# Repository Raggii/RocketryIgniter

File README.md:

# RocketryIgniter
To design and prototype a dual ignition system that can receive commands over UART and CANBUS. The device must be able to receive commands that arm and fire two separate but identical ignition circuits while also outputting its own system status. The design must attempt to be as compact as possible while also allowing for easy debugging.

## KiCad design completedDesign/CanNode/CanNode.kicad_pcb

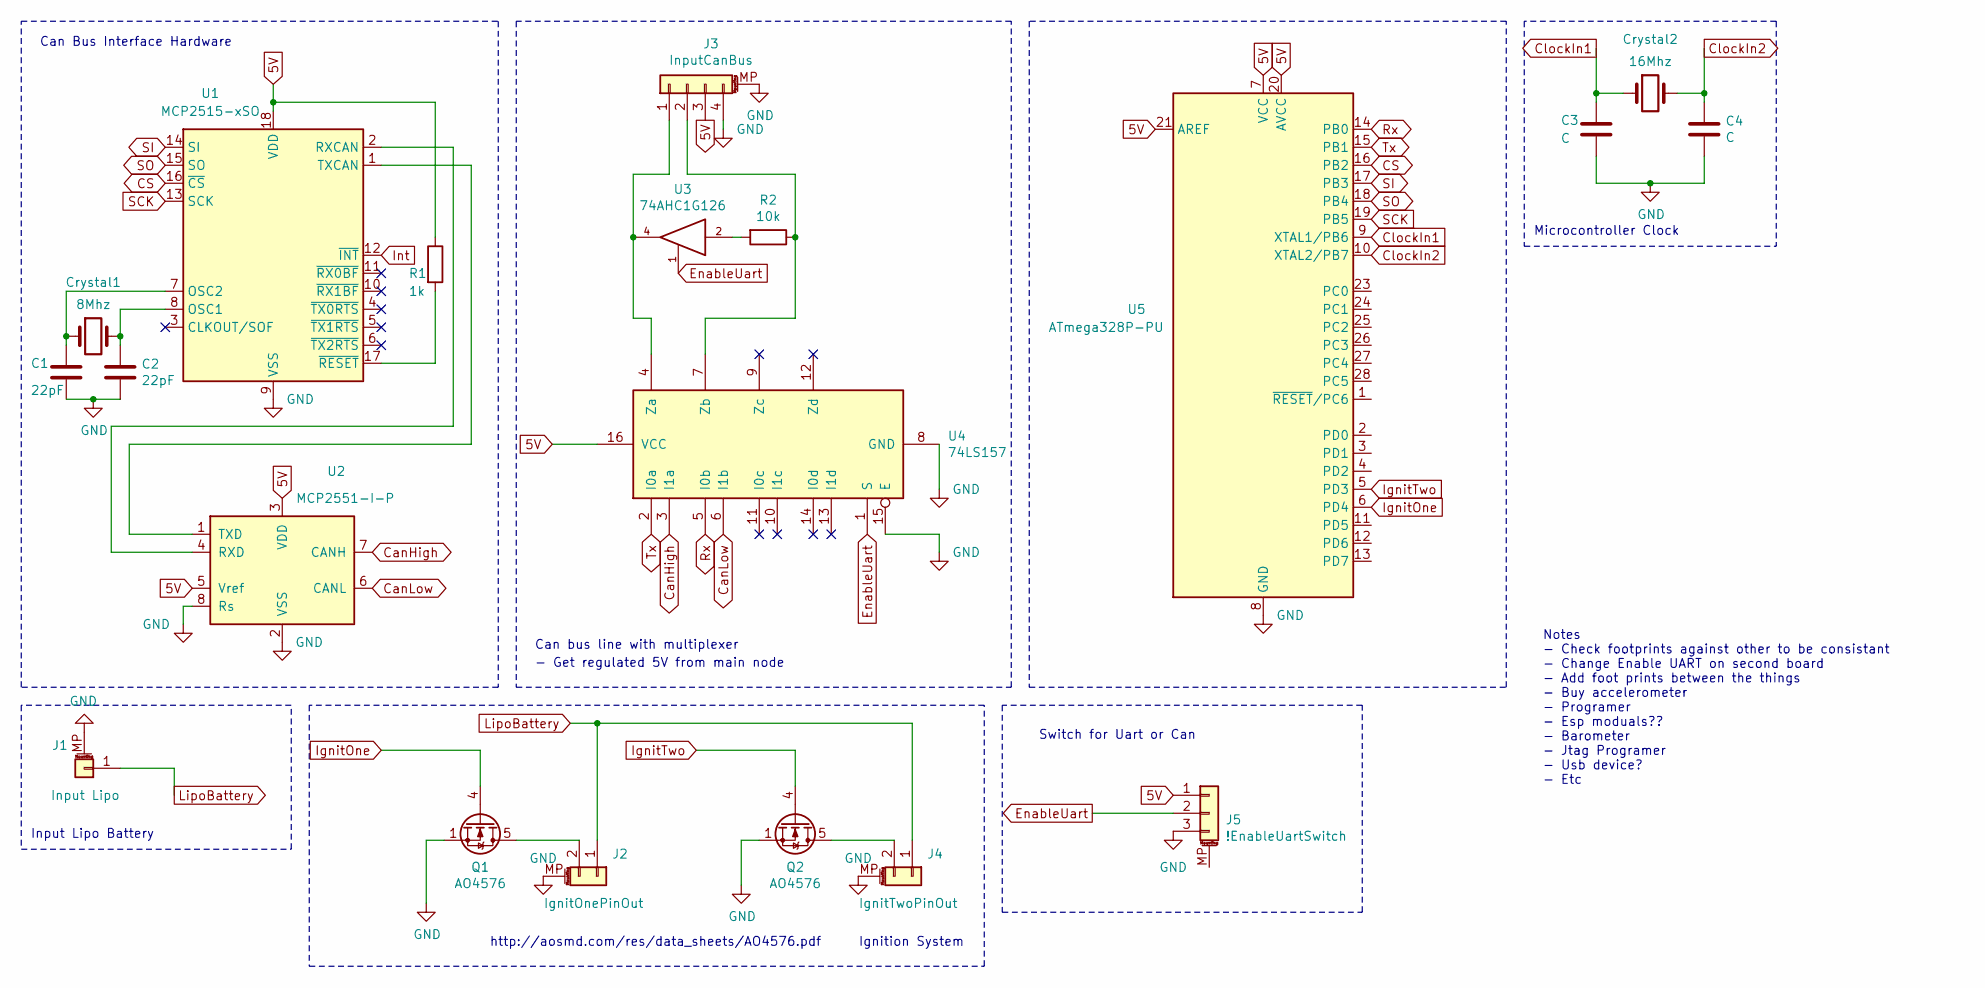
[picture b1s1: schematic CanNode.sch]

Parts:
C1, C2: 22pF; R_Axial_DIN0204_L3.6mm_D1.6mm_P2.54mm_Vertical
C3, C4: C; R_Axial_DIN0204_L3.6mm_D1.6mm_P2.54mm_Vertical
Crystal1: 8Mhz; Crystal_HC49-4H_Vertical
Crystal2: 16Mhz; Crystal_HC49-4H_Vertical
J1: Input Lipo; PinHeader_1x01_P2.00mm_Vertical
J2: IgnitOnePinOut; PinHeader_1x02_P2.00mm_Vertical
J3: InputCanBus; PinHeader_1x04_P2.00mm_Vertical
J4: IgnitTwoPinOut; PinHeader_1x02_P2.00mm_Vertical
J5: !EnableUartSwitch; PinHeader_1x03_P1.00mm_Vertical
Q1, Q2: AO4576; SOT-23-8_Handsoldering
R1: 1k; R_Axial_DIN0204_L3.6mm_D1.6mm_P5.08mm_Horizontal
R2: 10k; R_Axial_DIN0204_L3.6mm_D1.6mm_P5.08mm_Horizontal
U1: MCP2515-xSO; DIP-18_W7.62mm_LongPads
U2: MCP2551-I-P; DIP-8_W7.62mm
U3: 74AHC1G126; SOT65P210X110-5N
U4: 74LS157; DIP-16_W7.62mm_Socket_LongPads
U5: ATmega328P-PU; DIP-28_W7.62mm

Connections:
5V: J3.3, J5.1, R1.1, U1.18 (VDD), U2.3 (VDD), U2.5 (Vref), U4.16 (VCC), U5.7 (VCC), U5.20 (AVCC), U5.21 (AREF)
CS: U1.16 (~CS), U5.16 (PB2)
CanHigh: U2.7 (CANH), U4.3 (I1a)
CanLow: U2.6 (CANL), U4.6 (I1b)
ClockIn1: C3.1, Crystal2.1, U5.9 (XTAL1/PB6)
ClockIn2: C4.1, Crystal2.2, U5.10 (XTAL2/PB7)
EnableUart: J5.2, U3.1, U4.1 (S)
GND: C1.2, C2.2, C3.2, C4.2, J1.MP (MountPin), J2.MP (MountPin), J3.4, J3.MP (MountPin), J4.MP (MountPin), J5.3, Q1.1 (S), Q1.2 (S), Q1.3 (S), Q2.1 (S), Q2.2 (S), Q2.3 (S), U1.9 (VSS), U2.2 (VSS), U2.8 (Rs), U3.3 (GND), U4.8 (GND), U4.15 (E), U5.8 (GND), U5.22 (GND)
IgnitOne: Q1.4 (G), U5.6 (PD4)
IgnitTwo: Q2.4 (G), U5.5 (PD3)
Int: U1.12 (~INT)
LipoBattery: J1.1, J2.1, J4.1
unnamed: C1.1, Crystal1.1, U1.7 (OSC2)
unnamed: C2.1, Crystal1.2, U1.8 (OSC1)
unnamed: J2.2, Q1.5 (D)
unnamed: J3.1, U3.4, U4.4 (Za)
unnamed: J3.2, R2.1, U4.7 (Zb)
unnamed: J4.2, Q2.5 (D)
unnamed: R1.2, U1.17 (~RESET)
unnamed: R2.2, U3.2
unnamed: U1.1 (TXCAN), U2.1 (TXD)
unnamed: U1.2 (RXCAN), U2.4 (RXD)
Rx: U4.5 (I0b), U5.14 (PB0)
SCK: U1.13 (SCK), U5.19 (PB5)
SI: U1.14 (SI), U5.17 (PB3)
SO: U1.15 (SO), U5.18 (PB4)
Tx: U4.2 (I0a), U5.15 (PB1)
VCC: U3.5 (VCC)

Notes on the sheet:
Can Bus Interface Hardware
Can bus line with multiplexer
- Get regulated 5V from main node
Input Lipo Battery
Ignition System
http://aosmd.com/res/data_sheets/AO4576.pdf
Microcontroller Clock
Notes - Check footprints against other to be consistant - Change Enable UART on second board - Add foot prints between the things - Buy accelerometer - Programer - Esp moduals?? - Barometer - Jtag Programer - Usb device? - Etc
Switch for Uart or Can

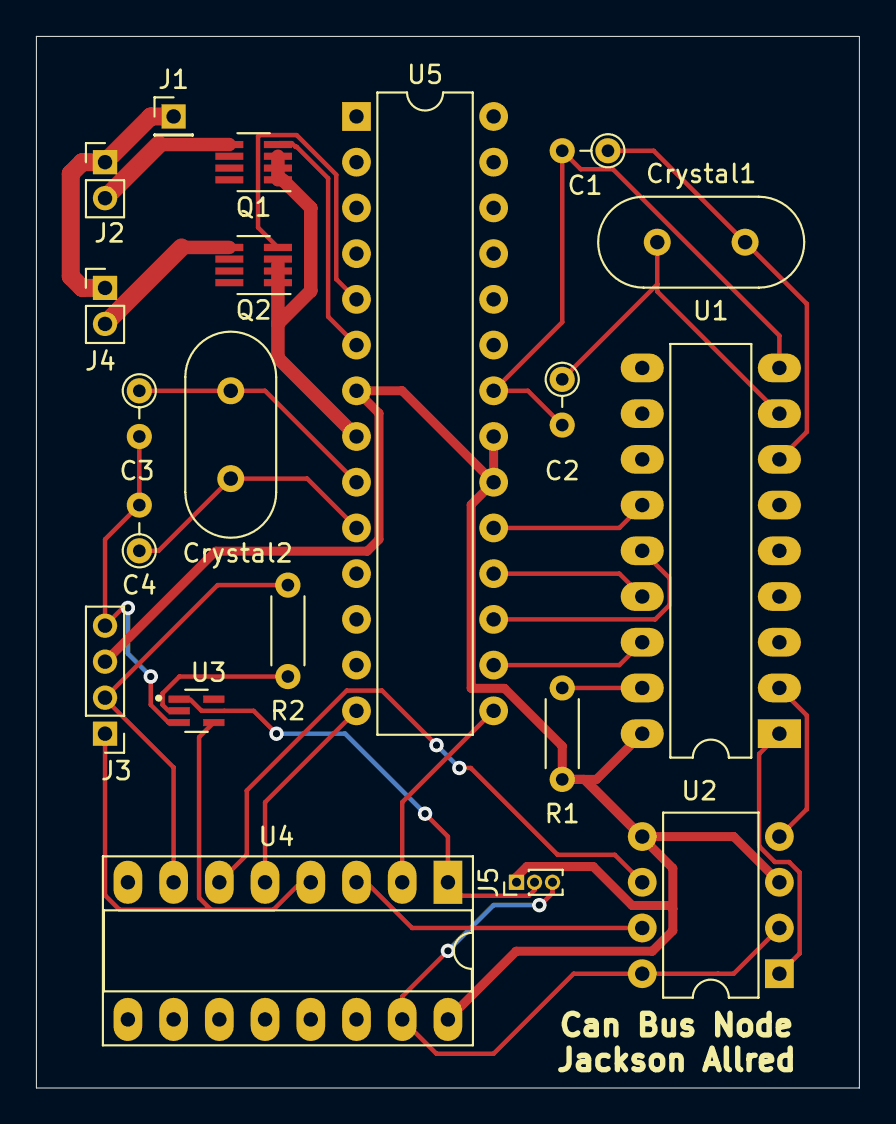
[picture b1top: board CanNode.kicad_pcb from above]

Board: 2 copper layers, 45.7 x 58.4 mm, 20 parts (0 on the bottom side), 26 nets.

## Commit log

2021-09-11 Add a Planning File
    This File is background research as well as general layout ideas for the project
2021-09-11 added more reasurch into the PHY as well as other components of the desgin
2021-09-12 added notes about STM microcontrollers as well as Uart communication \n in future add CanBus stuff
2021-10-03 Ideas for testing voltage measurement and regulator
    voltage measurement and regulation
2021-10-03 Shopping lost for canbus items
2021-10-03 Acquiring a programer this time
2021-10-03 Can we get a nucleoboard with can?
2021-10-03 The Circuit
    Wow speeelll right
2021-10-03 Updated schematic
2021-10-06 Testing22
2021-10-06 Added test arduino code
2021-10-07 Dan doesnt know how to git hub
2021-10-09 Added Second board
    A rough board
2021-10-11 Updated the foot prints
    Added notes also
2021-10-12 Updated the schematic somre more
    Hope u can get it finished tomorrow!!
2021-10-19 The fun code
    This is very clean code could be a little confusing but uber exciting
2021-10-20 Better code
2021-10-24 Final Upload
